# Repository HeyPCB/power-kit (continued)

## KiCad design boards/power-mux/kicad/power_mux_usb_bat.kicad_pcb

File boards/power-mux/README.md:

# Power Mux

USB-C first, a lithium cell as backup: a TPS2116 ideal-diode power mux with no diode drop and a pin that says which source is live.

| Layers | Size | Parts | Nets | Connections routed | Vias | ERC errors | DRC errors / unconnected / parity |
|---|---|---|---|---|---|---|---|
| 2 | 28 x 32 mm | 15 | 11 | 39 -> 0 open | 21 | 0 | 0 / 0 / 0 |

**Not fabricated, assembled or powered.** Every number on this page is measured by KiCad 10 on the files in this folder; the full measurements are in [`report.json`](report.json).

| | |
|---|---|
| KiCad project | [`kicad/`](kicad/) |
| Gerbers, BOM, CPL, STEP, schematic PDF | [`fab/`](fab/) |
| Renders | [top](media/top.png), [bottom](media/bottom.png) |
| Design process, every step as KiCad rendered it | [`media/design-process.mp4`](media/design-process.mp4) |

For a project that should keep running when the USB cable comes out: plug USB-C in and the load runs from USB; unplug it and a 1S cell on the JST PH connector takes over, with no Schottky drop and no current pushed back into either source. A TPS2116 in priority mode does the switching; the ST pin and a green LED tell the project when it is on the cell. OUT, GND, ST and the raw cell voltage are on a 2.54 mm header. Designed with the HeyPCB method on KiCad 10, by heypcb-kicad's headless pipeline with Freerouting 2.4.1, from the brief in `board.json`.

## Specs

- **Inputs:** USB-C 5 V (VIN1, 5.1k on CC1 and CC2, so any USB-C charger gives 5 V) and one Li-ion / LiPo cell on a JST S2B-PH-K connector (VIN2), + and - marked.
- **Switchover:** priority mode (MODE tied to VIN1). A 33k / 10k divider on PR1 hands over to the cell when USB falls below 1 V x 43 / 10 = 4.3 V, 3.96-4.64 V over the TPS2116's VREF tolerance (0.92-1.08 V, datasheet SLVSFG1A).
- **Switch:** TPS2116, 40 mOhm per channel, 2.5 A continuous, reverse-current blocking; break-before-make on switchover, so a large output capacitor or a hold-up cap on the load rides through the gap.
- **Status:** ST is open drain, pulled up to OUT through 100k: high on USB, low on the cell (and in thermal shutdown). The green BATT LED lights while on the cell.
- **Current paths:** VUSB, VBAT and OUT are copper zones from connector to cap to header; the mux's 0.5 mm-pitch leads are entered by short necks.
- **Board:** 28 x 32 mm, 2 layers, 1.6 mm.

## Parts

Every line carries an LCSC part number. Stock is JLCPCB's assembly stock on 2026-10-18.

| Designators | Value | LCSC | MPN | JLCPCB tier | Stock |
|---|---|---|---|---|---|
| C1,C4 | 10uF | C15850 | CL21A106KAYNNNE | Basic | 6,488,558 |
| C2,C3 | 1uF | C28323 | CL21B105KBFNNNE | Basic | 2,336,668 |
| D1 | Green (BATT) | C12624 | KT-0603G | Extended | 500,697 |
| J1 | USB-C | C165948 | TYPE-C-31-M-12 | Extended | 362,217 |
| J2 | BATT | C173752 | S2B-PH-K-S(LF)(SN) | Extended | 218,971 |
| J3 | OUT | C2691448 | PZ254V-11-04P | Extended | 887,837 |
| R1,R2 | 5.1k | C25905 | 0402WGF5101TCE | Basic | 5,089,075 |
| R3 | 33k | C4216 | 0603WAF3302T5E | Basic | 3,599,548 |
| R4 | 10k | C25804 | 0603WAF1002T5E | Basic | 39,984,479 |
| R5 | 100k | C25803 | 0603WAF1003T5E | Basic | 19,335,638 |
| R6 | 1k | C21190 | 0603WAF1001T5E | Basic | 23,225,827 |
| U1 | TPS2116 | C3235557 | TPS2116DRLR | Extended | 61,962 |

## Ordering

- PCB: upload `fab/power_mux_usb_bat_gerbers.zip`, 2 layers, 28 x 32 mm, 1.6 mm.
- Assembly: `fab/power_mux_usb_bat_bom.csv` and `fab/power_mux_usb_bat_cpl_jlc.csv`, top side.
- The CPL is fitted to each part's own JLCPCB footprint, pad by pad, and re-checked by laying each footprint where its row says: 15 of 15 rows fitted, worst pin-to-pad offset 0.10 mm.

## Notes

- Both inputs must stay within 1.6-5.5 V (6 V absolute maximum): USB 5 V and a single lithium cell. A 2S pack, a 9 V adapter or a USB PD source set above 5 V would destroy the TPS2116; this board's CC resistors ask a charger for 5 V only.
- No charger on this board: the cell is only discharged. Pair it with a charger, or use the cell's own charger.
- Not built or measured: the switchover threshold, the output dip during switchover and the 2.5 A rating are from the datasheet.
- The USB-C receptacle (HRO TYPE-C-31-M-12) renders as a plain box: KiCad's library footprint names a 3D model that KiCad does not ship. The footprint and its pads are KiCad's own and are fitted to JLCPCB's land.

## How it was made

Designed with the HeyPCB method on KiCad 10, by heypcb-kicad's headless pipeline with Freerouting 2.4.1, from the brief in [`board.json`](board.json).

## Licence

CERN-OHL-S-2.0, © 2026 heypcb.ai. See the collection's LICENSE.

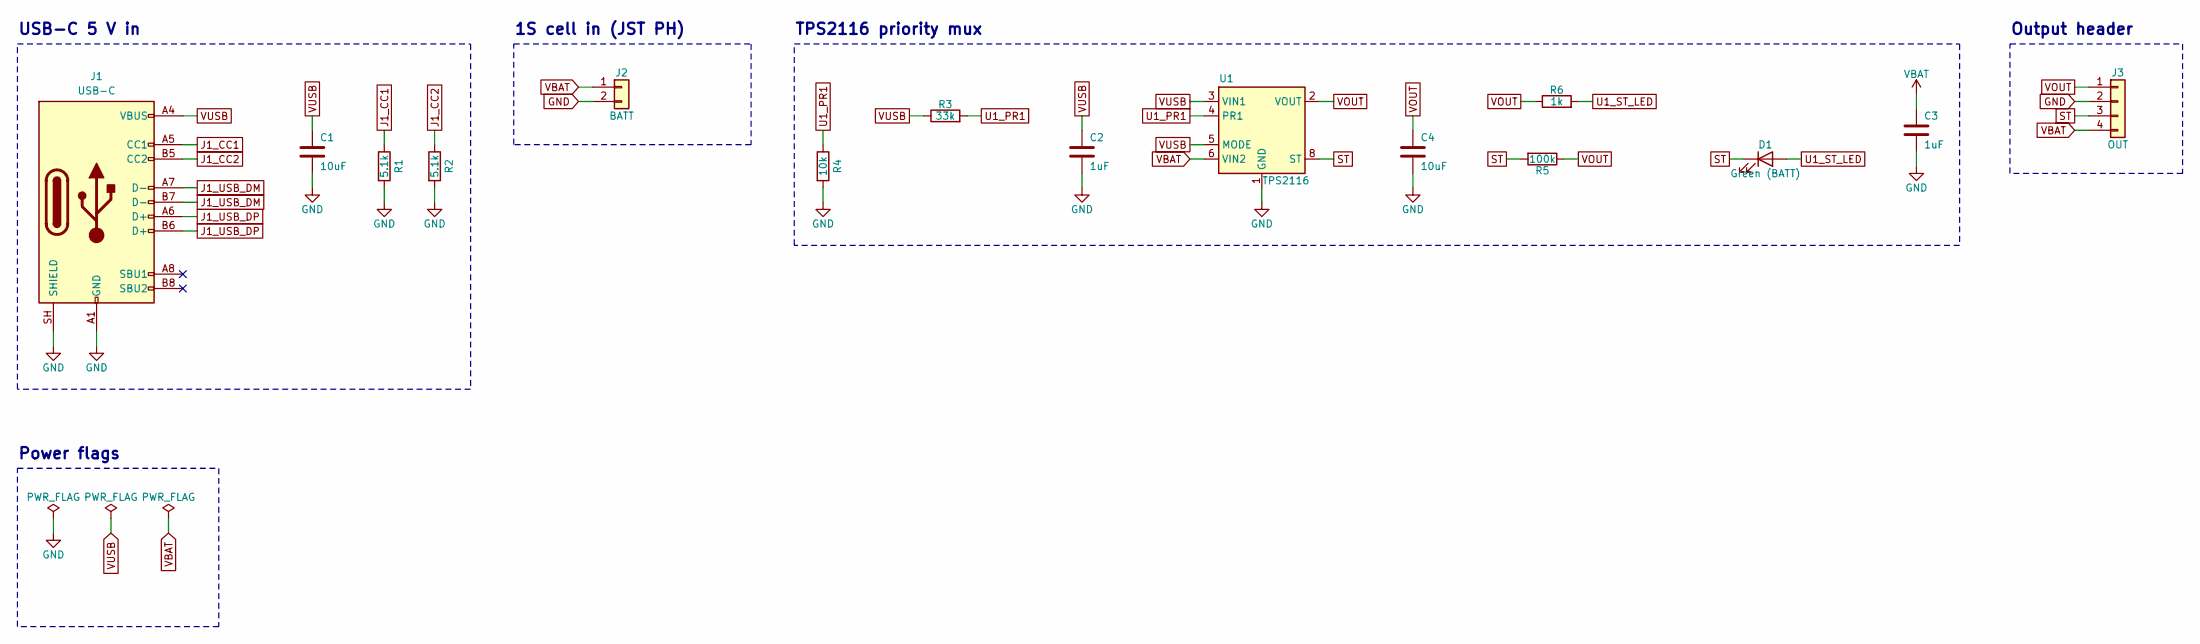
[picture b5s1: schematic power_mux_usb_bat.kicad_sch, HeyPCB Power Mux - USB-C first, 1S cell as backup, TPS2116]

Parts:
C1, C4: 10uF; C_0805_2012Metric; MPN CL21A106KAYNNNE; LCSC C15850
C2, C3: 1uF; C_0805_2012Metric; MPN CL21B105KBFNNNE; LCSC C28323
D1: Green (BATT); LED_0603_1608Metric; MPN KT-0603G; LCSC C12624
J1: USB-C; USB_C_Receptacle_HRO_TYPE-C-31-M-12; MPN TYPE-C-31-M-12; LCSC C165948
J2: BATT; JST_PH_S2B-PH-K_1x02_P2.00mm_Horizontal; MPN S2B-PH-K-S(LF)(SN); LCSC C173752
J3: OUT; PinHeader_1x04_P2.54mm_Vertical; MPN PZ254V-11-04P; LCSC C2691448
R1, R2: 5.1k; R_0402_1005Metric; MPN 0402WGF5101TCE; LCSC C25905
R3: 33k; R_0603_1608Metric; MPN 0603WAF3302T5E; LCSC C4216
R4: 10k; R_0603_1608Metric; MPN 0603WAF1002T5E; LCSC C25804
R5: 100k; R_0603_1608Metric; MPN 0603WAF1003T5E; LCSC C25803
R6: 1k; R_0603_1608Metric; MPN 0603WAF1001T5E; LCSC C21190
U1: TPS2116; SOT-583-8; MPN TPS2116DRLR; LCSC C3235557

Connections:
GND: C1.2, C2.2, C3.2, C4.2, J1.A1 (GND), J1.A12 (GND), J1.B1 (GND), J1.B12 (GND), J1.SH (SHIELD), J2.2, J3.2, R1.2, R2.2, R4.2, U1.1 (GND)
J1_CC1: J1.A5 (CC1), R1.1
J1_CC2: J1.B5 (CC2), R2.1
J1_USB_DM: J1.A7 (D-), J1.B7 (D-)
J1_USB_DP: J1.A6 (D+), J1.B6 (D+)
ST: D1.1 (K), J3.3, R5.2, U1.8 (ST)
U1_PR1: R3.2, R4.1, U1.4 (PR1)
U1_ST_LED: D1.2 (A), R6.2
VBAT: C3.1, J2.1, J3.4, U1.6 (VIN2)
VOUT: C4.1, J3.1, R5.1, R6.1, U1.2 (VOUT), U1.7 (VOUT)
VUSB: C1.1, C2.1, J1.A4 (VBUS), J1.A9 (VBUS), J1.B4 (VBUS), J1.B9 (VBUS), R3.1, U1.3 (VIN1), U1.5 (MODE)

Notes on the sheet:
USB-C 5 V in
1S cell in (JST PH)
TPS2116 priority mux
Output header
Power flags

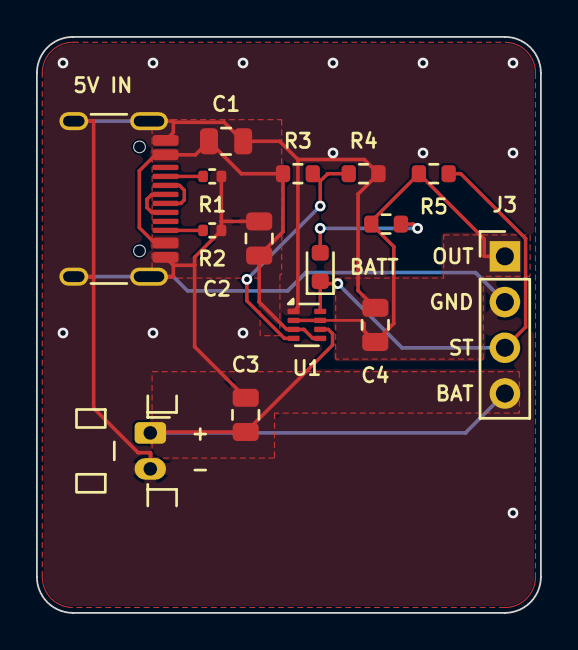
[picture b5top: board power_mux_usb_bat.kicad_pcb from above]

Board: 2 copper layers, 28.0 x 32.0 mm, 15 parts (0 on the bottom side), 11 nets.

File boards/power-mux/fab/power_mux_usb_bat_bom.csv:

"Reference","Value","Footprint","MPN","LCSC","Qty"
"C1,C4","10uF","Capacitor_SMD:C_0805_2012Metric","CL21A106KAYNNNE","C15850","2"
"C2,C3","1uF","Capacitor_SMD:C_0805_2012Metric","CL21B105KBFNNNE","C28323","2"
"D1","Green (BATT)","LED_SMD:LED_0603_1608Metric","KT-0603G","C12624","1"
"J1","USB-C","Connector_USB:USB_C_Receptacle_HRO_TYPE-C-31-M-12","TYPE-C-31-M-12","C165948","1"
"J2","BATT","Connector_JST:JST_PH_S2B-PH-K_1x02_P2.00mm_Horizontal","S2B-PH-K-S(LF)(SN)","C173752","1"
"J3","OUT","Connector_PinHeader_2.54mm:PinHeader_1x04_P2.54mm_Vertical","PZ254V-11-04P","C2691448","1"
"R1,R2","5.1k","Resistor_SMD:R_0402_1005Metric","0402WGF5101TCE","C25905","2"
"R3","33k","Resistor_SMD:R_0603_1608Metric","0603WAF3302T5E","C4216","1"
"R4","10k","Resistor_SMD:R_0603_1608Metric","0603WAF1002T5E","C25804","1"
"R5","100k","Resistor_SMD:R_0603_1608Metric","0603WAF1003T5E","C25803","1"
"R6","1k","Resistor_SMD:R_0603_1608Metric","0603WAF1001T5E","C21190","1"
"U1","TPS2116","Package_TO_SOT_SMD:SOT-583-8","TPS2116DRLR","C3235557","1"

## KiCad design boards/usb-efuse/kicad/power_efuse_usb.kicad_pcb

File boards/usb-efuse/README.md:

# USB eFuse

A 5 V eFuse between a USB-C supply and your project: about 2 A current limit, output clamped at 6.1 V, rides out a 20 V input, soft start and auto-retry.

| Layers | Size | Parts | Nets | Connections routed | Vias | ERC errors | DRC errors / unconnected / parity |
|---|---|---|---|---|---|---|---|
| 2 | 26 x 30 mm | 15 | 11 | 39 -> 0 open | 22 | 0 | 0 / 0 / 0 |

**Not fabricated, assembled or powered.** Every number on this page is measured by KiCad 10 on the files in this folder; the full measurements are in [`report.json`](report.json).

| | |
|---|---|
| KiCad project | [`kicad/`](kicad/) |
| Gerbers, BOM, CPL, STEP, schematic PDF | [`fab/`](fab/) |
| Renders | [top](media/top.png), [bottom](media/bottom.png) |
| Design process, every step as KiCad rendered it | [`media/design-process.mp4`](media/design-process.mp4) |

The protection a bench project, a LED strip or a motor driver should have between it and a USB charger: a short or an overload is limited to about 2 A and retried instead of pulling the supply down, a charger or cable that puts more than 5 V on VBUS is clamped to 6.1 V at the output, and the load's capacitors charge through a soft start. USB-C in on the left, a 5 mm screw terminal out on the right, a green LED when the output is on. Designed with the HeyPCB method on KiCad 10, by heypcb-kicad's headless pipeline with Freerouting 2.4.1, from the brief in `board.json`.

## Specs

- **Input:** USB-C, 5.1k on CC1 and CC2 (a USB-C charger gives 5 V). The TPS259251 is rated to 20 V on its input (22 V for under 1 ms) and runs from 4.5-5.5 V.
- **Current limit:** RILIM 45.3k: 2.05 A typical, 1.72-2.42 A (TPS25925x datasheet, at VIN-OUT 5 V). Auto-retry after an overload or thermal shutdown.
- **Over-voltage:** the output is clamped at 6.1 V (TPS259251); undervoltage lockout at 4.3 V (default, 1 M from VIN to EN/UVLO).
- **Soft start:** 10 nF on dV/dT; output cap 10 uF.
- **Output:** 5 mm MaiXu MX126 screw terminal, + and - marked, SMBJ24A TVS and 1 uF across it, green LED.
- **Current paths:** VUSB is a zone on both layers, stitched, from the receptacle's four VBUS pins to the eFuse's VIN pins; VOUT is a zone from its OUT pins to the terminal and the TVS.
- **Board:** 26 x 30 mm, 2 layers, 1.6 mm.

## Parts

Every line carries an LCSC part number. Stock is JLCPCB's assembly stock on 2026-10-18.

| Designators | Value | LCSC | MPN | JLCPCB tier | Stock |
|---|---|---|---|---|---|
| C1,C3 | 10uF | C15850 | CL21A106KAYNNNE | Basic | 6,484,766 |
| C2,C5 | 1uF | C28323 | CL21B105KBFNNNE | Basic | 2,336,678 |
| C4 | 10nF | C15195 | CL05B103KB5NNNC | Basic | 6,125,751 |
| D1 | SMBJ24A | C123819 | SMBJ24A | Extended | 59,843 |
| D2 | Green (OUT) | C12624 | KT-0603G | Extended | 500,697 |
| J1 | USB-C | C165948 | TYPE-C-31-M-12 | Extended | 362,219 |
| J2 | OUT | C5188434 | MX126-5.0-02P-GN01-Cu-S-A | Extended | 35,962 |
| R1,R2 | 5.1k | C25905 | 0402WGF5101TCE | Basic | 5,088,156 |
| R3 | 1M | C22935 | 0603WAF1004T5E | Basic | 5,598,120 |
| R4 | 45.3k | C23058 | 0603WAF4532T5E | Extended | 64,416 |
| R5 | 2.2k | C4190 | 0603WAF2201T5E | Basic | 6,541,337 |
| U1 | TPS259251 | C527680 | TPS259251DRCR | Extended | 2,748 |

## Ordering

- PCB: upload `fab/power_efuse_usb_gerbers.zip`, 2 layers, 26 x 30 mm, 1.6 mm.
- Assembly: `fab/power_efuse_usb_bom.csv` and `fab/power_efuse_usb_cpl_jlc.csv`, top side.
- The CPL is fitted to each part's own JLCPCB footprint, pad by pad, and re-checked by laying each footprint where its row says: 15 of 15 rows fitted, worst pin-to-pad offset 0.21 mm.

## Notes

- The TPS259251DRCR (C527680) had 2,748 in JLCPCB's stock when this was packaged, the lowest on the parts list. Check it before ordering.
- A 20 V input is survived, not passed: the output clamps at 6.1 V and the eFuse drops the rest across itself, so with a load it heats and may cycle through thermal shutdown and auto-retry. It is a fault condition, not an operating mode.
- The USB-C receptacle (HRO TYPE-C-31-M-12) renders as a plain box: KiCad's library footprint names a 3D model that KiCad does not ship. The footprint and its pads are KiCad's own and are fitted to JLCPCB's land.
- Not built or measured: the current limit and the clamp are datasheet figures.

## How it was made

Designed with the HeyPCB method on KiCad 10, by heypcb-kicad's headless pipeline with Freerouting 2.4.1, from the brief in [`board.json`](board.json).

## Licence

CERN-OHL-S-2.0, © 2026 heypcb.ai. See the collection's LICENSE.

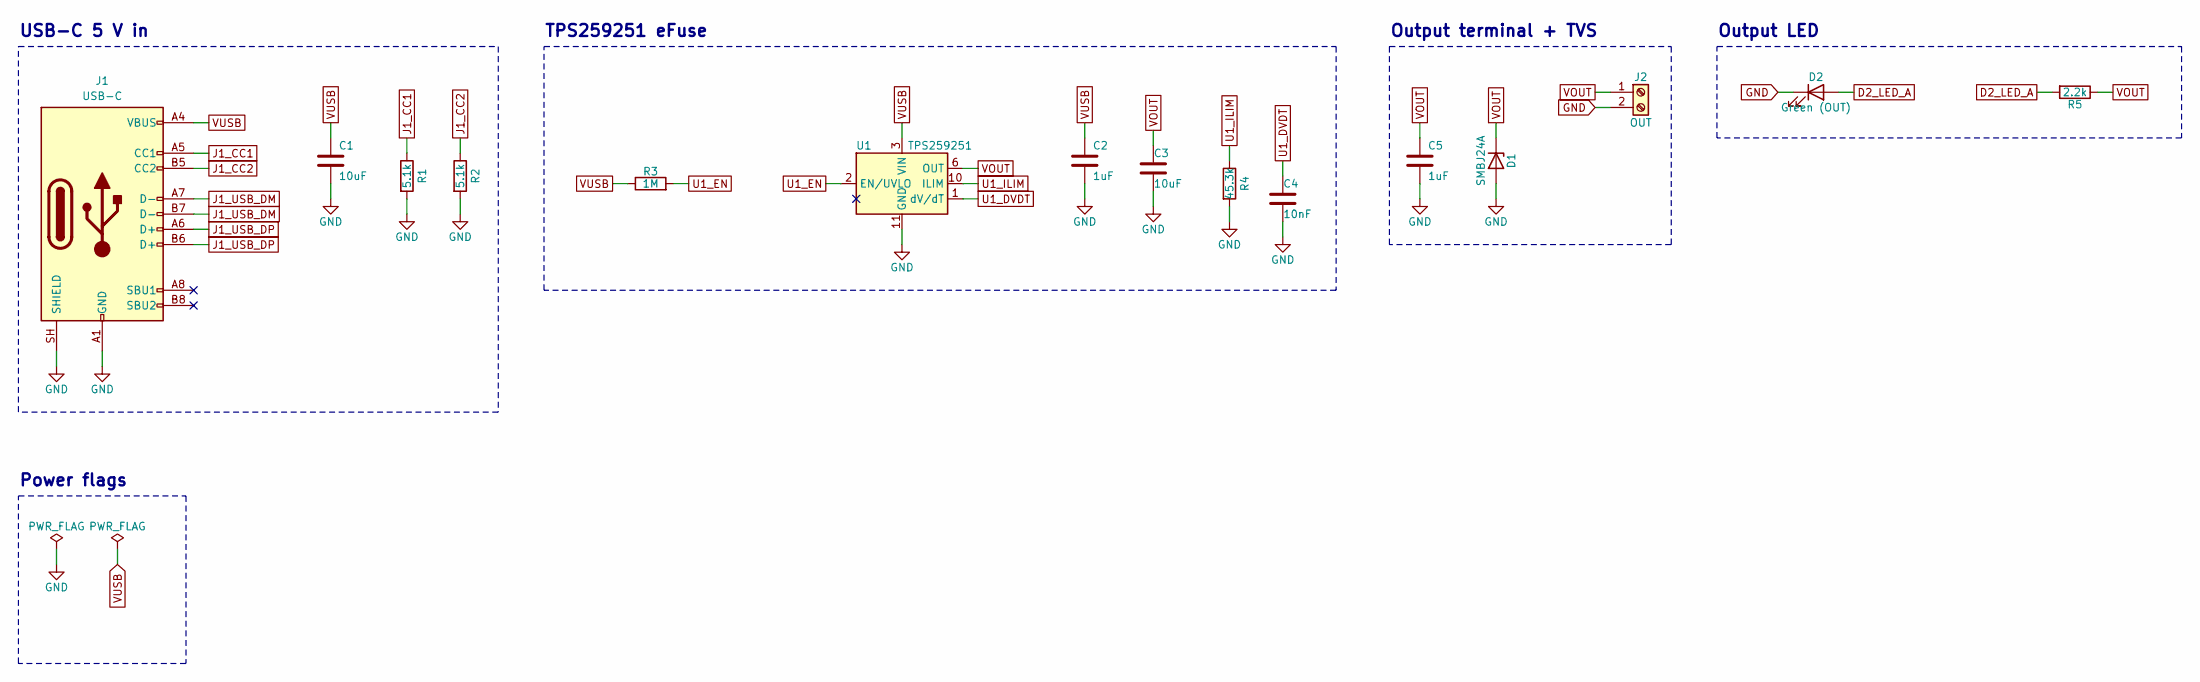
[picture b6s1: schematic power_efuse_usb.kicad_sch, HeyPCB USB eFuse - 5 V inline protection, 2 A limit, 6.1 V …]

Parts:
C1, C3: 10uF; C_0805_2012Metric; MPN CL21A106KAYNNNE; LCSC C15850
C2, C5: 1uF; C_0805_2012Metric; MPN CL21B105KBFNNNE; LCSC C28323
C4: 10nF; C_0402_1005Metric; MPN CL05B103KB5NNNC; LCSC C15195
D1: SMBJ24A; D_SMB; MPN SMBJ24A; LCSC C123819
D2: Green (OUT); LED_0603_1608Metric; MPN KT-0603G; LCSC C12624
J1: USB-C; USB_C_Receptacle_HRO_TYPE-C-31-M-12; MPN TYPE-C-31-M-12; LCSC C165948
J2: OUT; TerminalBlock_MaiXu_MX126-5.0-02P_1x02_P5.00mm; MPN MX126-5.0-02P-GN01-Cu-S-A; LCSC C5188434
R1, R2: 5.1k; R_0402_1005Metric; MPN 0402WGF5101TCE; LCSC C25905
R3: 1M; R_0603_1608Metric; MPN 0603WAF1004T5E; LCSC C22935
R4: 45.3k; R_0603_1608Metric; MPN 0603WAF4532T5E; LCSC C23058
R5: 2.2k; R_0603_1608Metric; MPN 0603WAF2201T5E; LCSC C4190
U1: TPS259251; VSON-10-1EP_3x3mm_P0.5mm_EP1.65x2.4mm; MPN TPS259251DRCR; LCSC C527680

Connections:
D2_LED_A: D2.2 (A), R5.2
GND: C1.2, C2.2, C3.2, C4.2, C5.2, D1.2 (A), D2.1 (K), J1.A1 (GND), J1.A12 (GND), J1.B1 (GND), J1.B12 (GND), J1.SH (SHIELD), J2.2, R1.2, R2.2, R4.2, U1.11 (GND)
J1_CC1: J1.A5 (CC1), R1.1
J1_CC2: J1.B5 (CC2), R2.1
J1_USB_DM: J1.A7 (D-), J1.B7 (D-)
J1_USB_DP: J1.A6 (D+), J1.B6 (D+)
U1_DVDT: C4.1, U1.1 (dV/dT)
U1_EN: R3.2, U1.2 (EN/UVLO)
U1_ILIM: R4.1, U1.10 (ILIM)
VOUT: C3.1, C5.1, D1.1 (K), J2.1, R5.1, U1.6 (OUT), U1.7 (OUT), U1.8 (OUT)
VUSB: C1.1, C2.1, J1.A4 (VBUS), J1.A9 (VBUS), J1.B4 (VBUS), J1.B9 (VBUS), R3.1, U1.3 (VIN), U1.4 (VIN), U1.5 (VIN)

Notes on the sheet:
USB-C 5 V in
TPS259251 eFuse
Output terminal + TVS
Output LED
Power flags

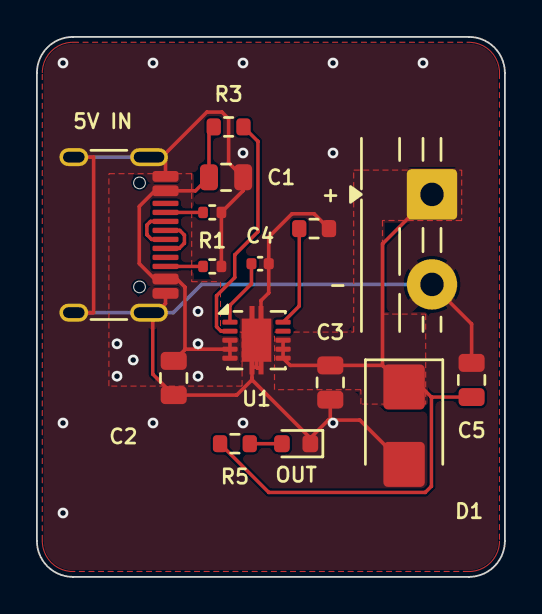
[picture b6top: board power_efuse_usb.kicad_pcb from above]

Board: 2 copper layers, 26.0 x 30.0 mm, 15 parts (0 on the bottom side), 11 nets.

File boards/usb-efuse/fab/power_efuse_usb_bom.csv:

"Reference","Value","Footprint","MPN","LCSC","Qty"
"C1,C3","10uF","Capacitor_SMD:C_0805_2012Metric","CL21A106KAYNNNE","C15850","2"
"C2,C5","1uF","Capacitor_SMD:C_0805_2012Metric","CL21B105KBFNNNE","C28323","2"
"C4","10nF","Capacitor_SMD:C_0402_1005Metric","CL05B103KB5NNNC","C15195","1"
"D1","SMBJ24A","Diode_SMD:D_SMB","SMBJ24A","C123819","1"
"D2","Green (OUT)","LED_SMD:LED_0603_1608Metric","KT-0603G","C12624","1"
"J1","USB-C","Connector_USB:USB_C_Receptacle_HRO_TYPE-C-31-M-12","TYPE-C-31-M-12","C165948","1"
"J2","OUT","TerminalBlock:TerminalBlock_MaiXu_MX126-5.0-02P_1x02_P5.00mm","MX126-5.0-02P-GN01-Cu-S-A","C5188434","1"
"R1,R2","5.1k","Resistor_SMD:R_0402_1005Metric","0402WGF5101TCE","C25905","2"
"R3","1M","Resistor_SMD:R_0603_1608Metric","0603WAF1004T5E","C22935","1"
"R4","45.3k","Resistor_SMD:R_0603_1608Metric","0603WAF4532T5E","C23058","1"
"R5","2.2k","Resistor_SMD:R_0603_1608Metric","0603WAF2201T5E","C4190","1"
"U1","TPS259251","Package_SON:VSON-10-1EP_3x3mm_P0.5mm_EP1.65x2.4mm","TPS259251DRCR","C527680","1"
